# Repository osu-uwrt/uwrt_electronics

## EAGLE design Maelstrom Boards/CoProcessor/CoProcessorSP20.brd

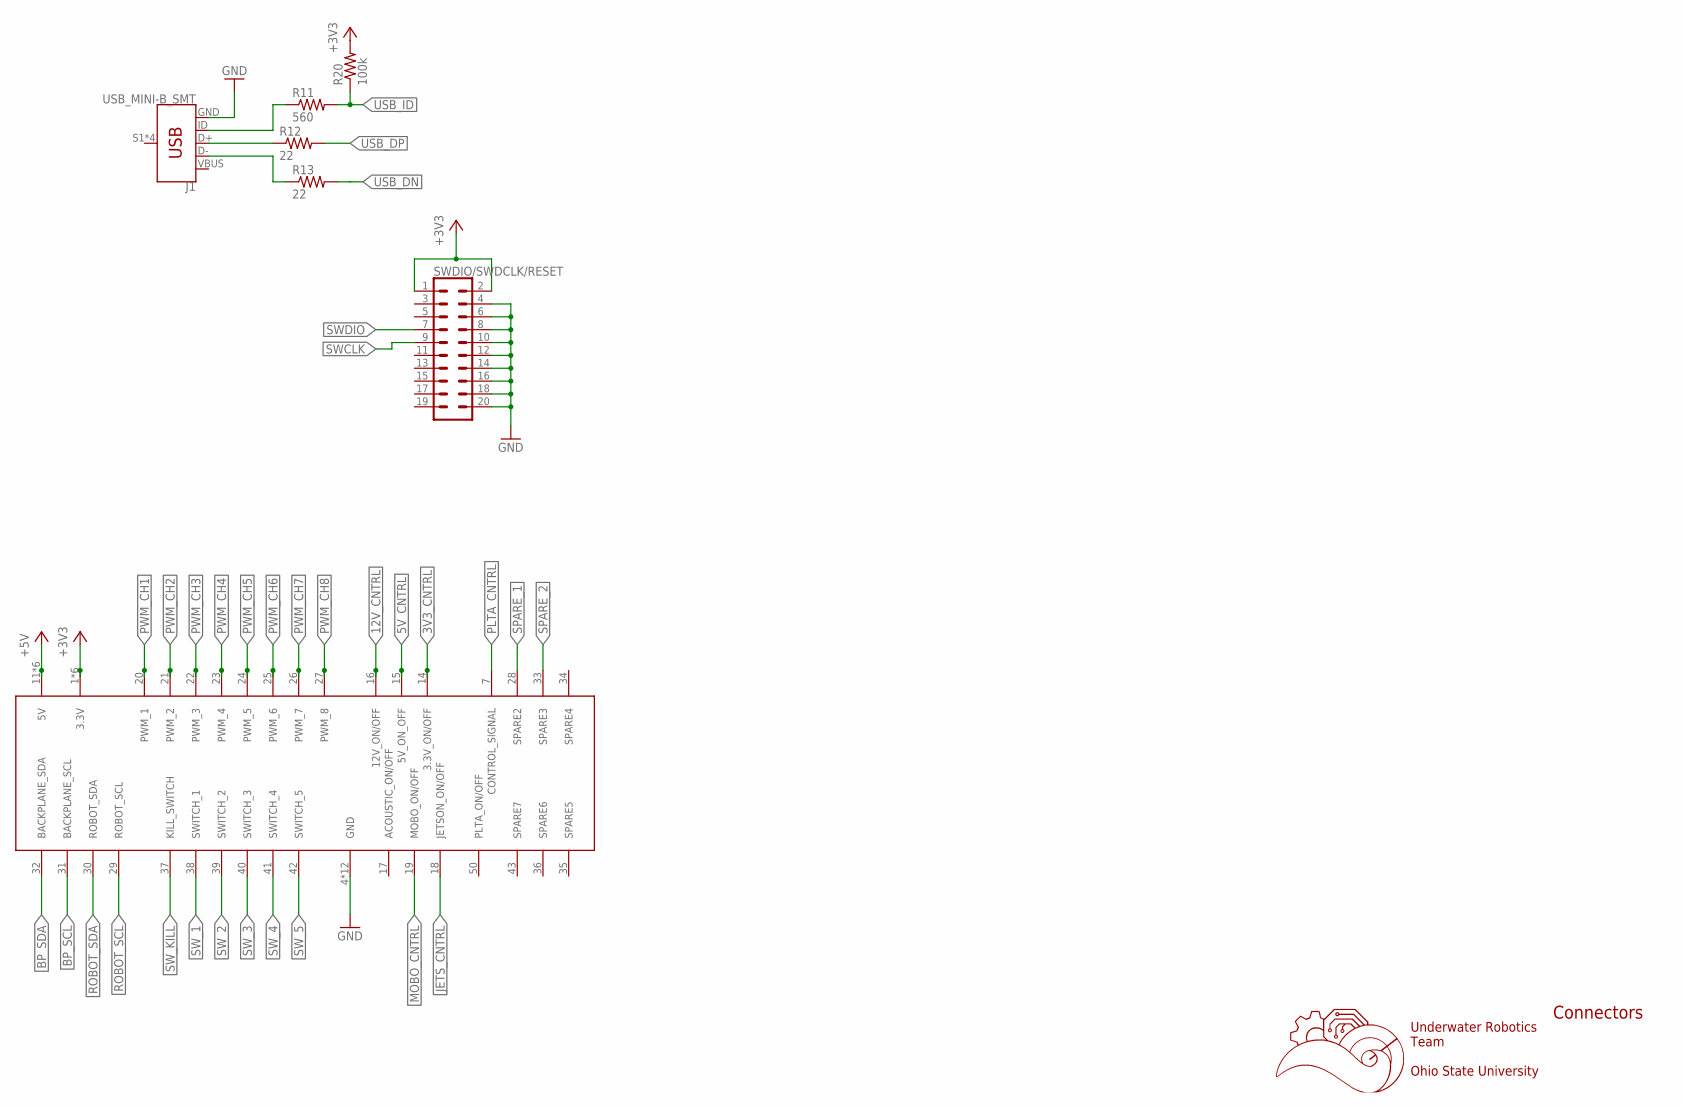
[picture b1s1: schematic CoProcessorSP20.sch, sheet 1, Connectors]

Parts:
J1: USB_MINI-B_SMT; USB-MINIB
R11: 560; R0603
R12, R13: 22; R0603
R20: 100k; R0603
SWDIO/SWDCLK/RESET: CONN_10X2; 2X10
U$1: 5530843-EDGE; 5530843-6-BOARDFINGERS

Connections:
3V3_CNTRL: U$1.14 (3.3V_ON/OFF); also elsewhere on the board
5V_CNTRL: U$1.15 (5V_ON_OFF); also elsewhere on the board
12V_CNTRL: U$1.16 (12V_ON/OFF); also elsewhere on the board
+3V3: R20.2, SWDIO/SWDCLK/RESET.1, SWDIO/SWDCLK/RESET.2, U$1.1 (3.3V), U$1.2 (3.3V), U$1.3 (3.3V), U$1.54 (3.3V), U$1.55 (3.3V), U$1.56 (3.3V); also elsewhere on the board
+5V: U$1.11 (5V), U$1.12 (5V), U$1.13 (5V), U$1.44 (5V), U$1.45 (5V), U$1.46 (5V)
BP_SCL: U$1.31 (BACKPLANE_SCL); also elsewhere on the board
BP_SDA: U$1.32 (BACKPLANE_SDA); also elsewhere on the board
GND: J1.GND, SWDIO/SWDCLK/RESET.4, SWDIO/SWDCLK/RESET.6, SWDIO/SWDCLK/RESET.8, SWDIO/SWDCLK/RESET.10, SWDIO/SWDCLK/RESET.12, SWDIO/SWDCLK/RESET.14, SWDIO/SWDCLK/RESET.16, SWDIO/SWDCLK/RESET.18, SWDIO/SWDCLK/RESET.20, U$1.4 (GND), U$1.5 (GND), U$1.6 (GND), U$1.8 (GND), U$1.9 (GND), U$1.10 (GND), U$1.47 (GND), U$1.48 (GND), U$1.49 (GND), U$1.51 (GND), U$1.52 (GND), U$1.53 (GND); also elsewhere on the board
JETS_CNTRL: U$1.18 (JETSON_ON/OFF); also elsewhere on the board
MOBO_CNTRL: U$1.19 (MOBO_ON/OFF); also elsewhere on the board
unnamed: J1.ID, R11.1
unnamed: J1.D+, R12.1
unnamed: J1.D-, R13.1
PLTA_CNTRL: U$1.7 (CONTROL_SIGNAL); also elsewhere on the board
PWM_CH1: U$1.20 (PWM_1); also elsewhere on the board
PWM_CH2: U$1.21 (PWM_2); also elsewhere on the board
PWM_CH3: U$1.22 (PWM_3); also elsewhere on the board
PWM_CH4: U$1.23 (PWM_4); also elsewhere on the board
PWM_CH5: U$1.24 (PWM_5); also elsewhere on the board
PWM_CH6: U$1.25 (PWM_6); also elsewhere on the board
PWM_CH7: U$1.26 (PWM_7); also elsewhere on the board
PWM_CH8: U$1.27 (PWM_8); also elsewhere on the board
ROBOT_SCL: U$1.29 (ROBOT_SCL); also elsewhere on the board
ROBOT_SDA: U$1.30 (ROBOT_SDA); also elsewhere on the board
SPARE_1: U$1.28 (SPARE2); also elsewhere on the board
SPARE_2: U$1.33 (SPARE3); also elsewhere on the board
SWCLK: SWDIO/SWDCLK/RESET.9; also elsewhere on the board
SWDIO: SWDIO/SWDCLK/RESET.7; also elsewhere on the board
SW_1: U$1.38 (SWITCH_1); also elsewhere on the board
SW_2: U$1.39 (SWITCH_2); also elsewhere on the board
SW_3: U$1.40 (SWITCH_3); also elsewhere on the board
SW_4: U$1.41 (SWITCH_4); also elsewhere on the board
SW_5: U$1.42 (SWITCH_5); also elsewhere on the board
SW_KILL: U$1.37 (KILL_SWITCH); also elsewhere on the board
USB_DN: R13.2; also elsewhere on the board
USB_DP: R12.2; also elsewhere on the board
USB_ID: R11.2, R20.1
VBUS: J1.VBUS

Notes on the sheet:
Underwater Robotics Team Ohio State University
Connectors

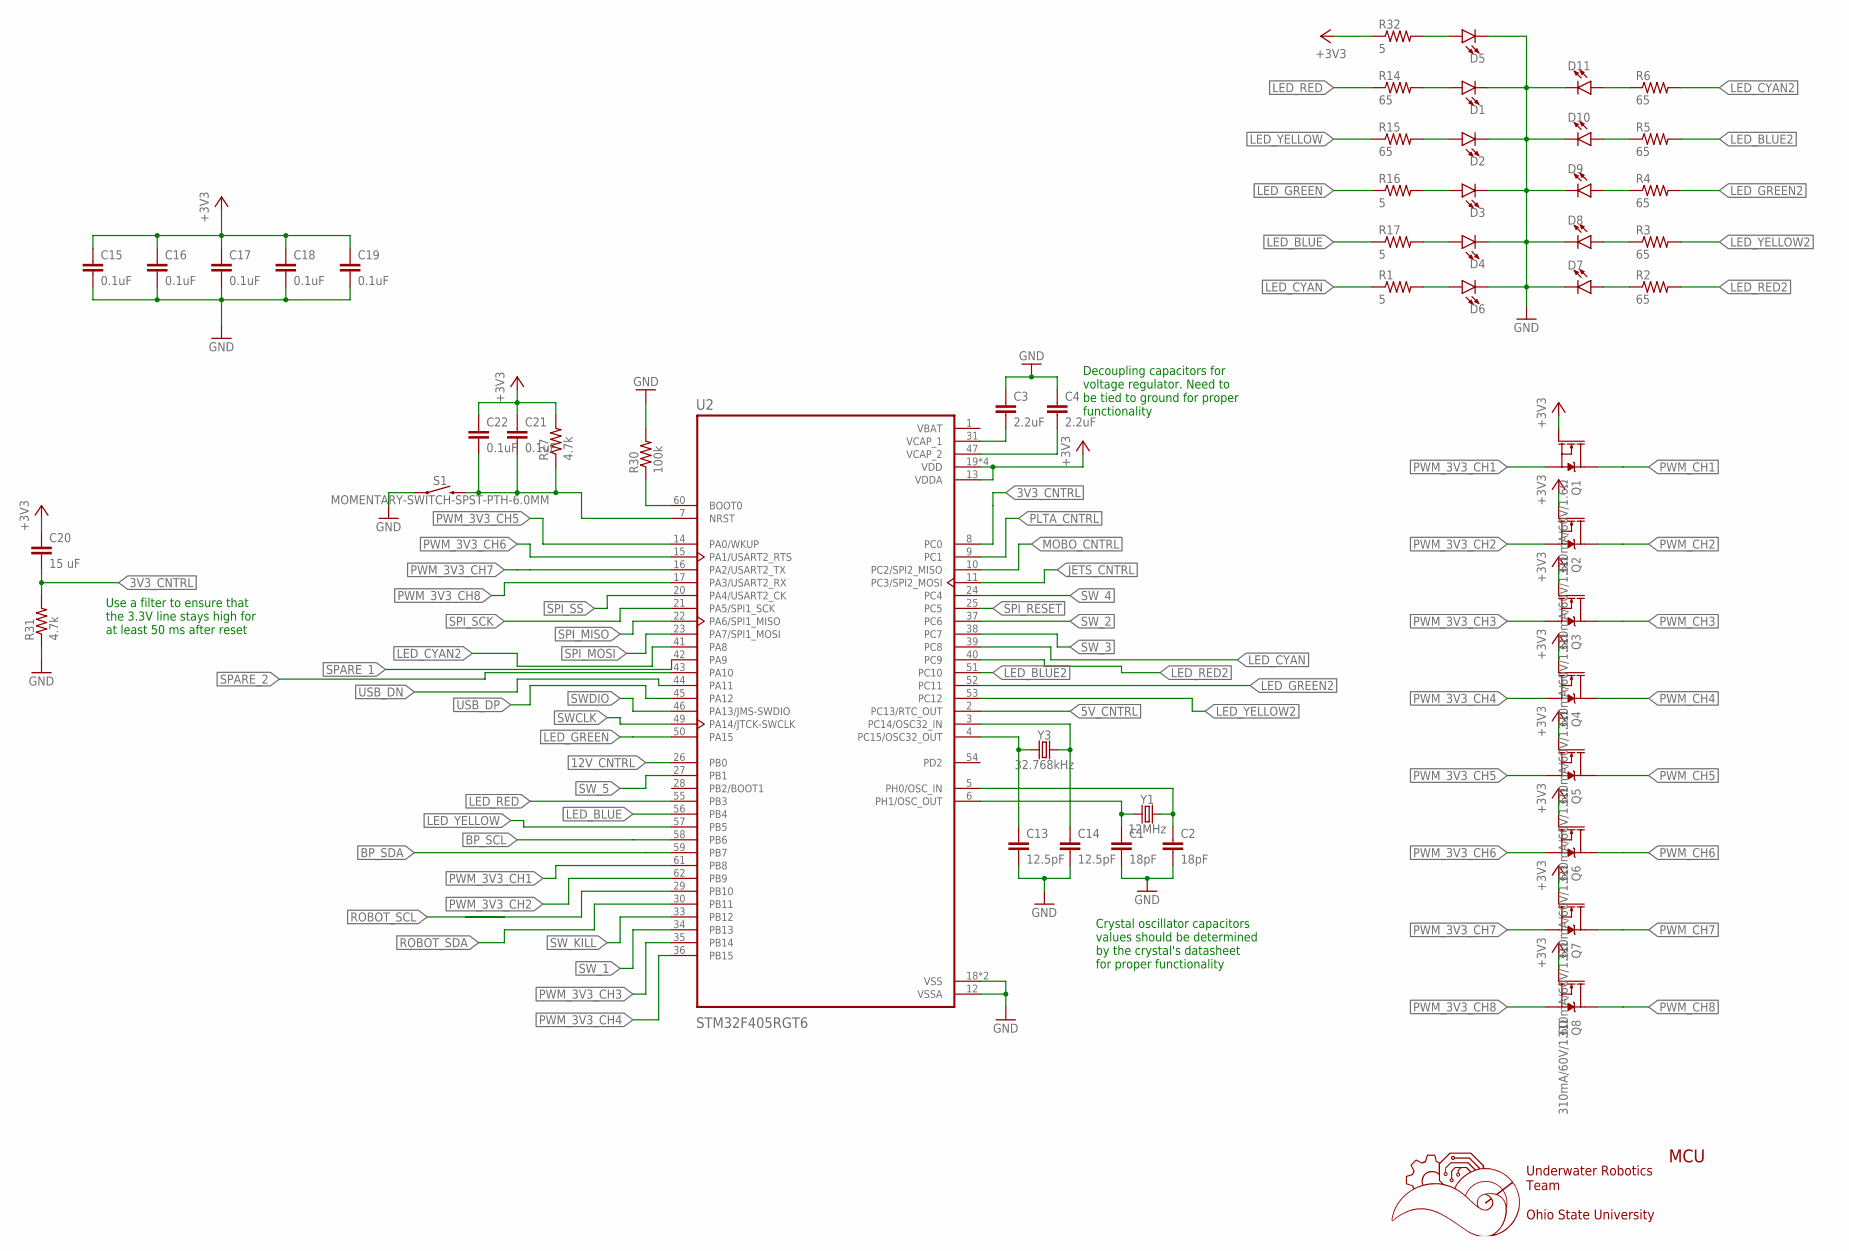
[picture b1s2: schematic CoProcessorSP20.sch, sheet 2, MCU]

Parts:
C1, C2: 18pF; C0603
C3, C4: 2.2uF; C0603
C13, C14: 12.5pF; C0603
C15, C16, C17, C18, C19, C21, C22: 0.1uF; C0603
C20: 15 uF; C050-025X075
D1, D2, D3, D4, D5, D6, D7, D8, D9, D10, D11: LED0603; LED-0603
Q1, Q2, Q3, Q4, Q5, Q6, Q7, Q8: 310mA/60V/1.6Ω; SOT323
R1, R16, R17, R32: 5; R0603
R2, R3, R4, R5, R6, R14, R15: 65; R0603
R27, R31: 4.7k; R0603
R30: 100k; R0603
S1: MOMENTARY-SWITCH-SPST-PTH-6.0MM; TACTILE_SWITCH_PTH_6.0MM
U2: STM32F405RGT6; QFP50P1200X1200X160-64N
Y1: 12MHz; HC49US
Y3: 32.768kHz; CRYSTAL-SMD-3.2X1.5MM

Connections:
3V3_CNTRL: C20.2, R31.2, U2.8 (PC0); also elsewhere on the board
5V_CNTRL: U2.2 (PC13/RTC_OUT); also elsewhere on the board
12V_CNTRL: U2.26 (PB0); also elsewhere on the board
+3V3: C15.1, C16.1, C17.1, C18.1, C19.1, C20.1, C21.1, C22.1, Q1.1 (G), Q2.1 (G), Q3.1 (G), Q4.1 (G), Q5.1 (G), Q6.1 (G), Q7.1 (G), Q8.1 (G), R27.2, R32.1, U2.13 (VDDA), U2.19 (VDD), U2.32 (VDD), U2.48 (VDD), U2.64 (VDD); also elsewhere on the board
BP_SCL: U2.58 (PB6); also elsewhere on the board
BP_SDA: U2.59 (PB7); also elsewhere on the board
GND: C1.2, C2.2, C3.1, C4.1, C13.2, C14.2, C15.2, C16.2, C17.2, C18.2, C19.2, D1.C, D2.C, D3.C, D4.C, D5.C, D6.C, D7.C, D8.C, D9.C, D10.C, D11.C, R30.2, R31.1, S1.1, U2.12 (VSSA), U2.18 (VSS), U2.63 (VSS); also elsewhere on the board
JETS_CNTRL: U2.11 (PC3/SPI2_MOSI); also elsewhere on the board
LED_BLUE: R17.1, U2.56 (PB4)
LED_BLUE2: R5.2, U2.51 (PC10)
LED_CYAN: R1.1, U2.39 (PC8)
LED_CYAN2: R6.2, U2.41 (PA8)
LED_GREEN: R16.1, U2.50 (PA15)
LED_GREEN2: R4.2, U2.52 (PC11)
LED_RED: R14.1, U2.55 (PB3)
LED_RED2: R2.2, U2.40 (PC9)
LED_YELLOW: R15.1, U2.57 (PB5)
LED_YELLOW2: R3.2, U2.53 (PC12)
MOBO_CNTRL: U2.10 (PC2/SPI2_MISO); also elsewhere on the board
unnamed: C1.1, U2.6 (PH1/OSC_OUT), Y1.1
unnamed: D1.A, R14.2
unnamed: D2.A, R15.2
unnamed: D3.A, R16.2
unnamed: D4.A, R17.2
unnamed: C2.1, U2.5 (PH0/OSC_IN), Y1.2
unnamed: C4.2, U2.47 (VCAP_2)
unnamed: C3.2, U2.31 (VCAP_1)
unnamed: C13.1, U2.4 (PC15/OSC32_OUT), Y3.P$1 (1)
unnamed: C14.1, U2.3 (PC14/OSC32_IN), Y3.P$2 (2)
unnamed: R30.1, U2.60 (BOOT0)
unnamed: D5.A, R32.2
unnamed: D6.A, R1.2
unnamed: D7.A, R2.1
unnamed: C21.2, C22.2, R27.1, S1.3 (2), U2.7 (NRST)
unnamed: D8.A, R3.1
unnamed: D9.A, R4.1
unnamed: D10.A, R5.1
unnamed: D11.A, R6.1
PLTA_CNTRL: U2.9 (PC1); also elsewhere on the board
PWM_3V3_CH1: Q1.2 (S), U2.61 (PB8)
PWM_3V3_CH2: Q2.2 (S), U2.62 (PB9)
PWM_3V3_CH3: Q3.2 (S), U2.35 (PB14)
PWM_3V3_CH4: Q4.2 (S), U2.36 (PB15)
PWM_3V3_CH5: Q5.2 (S), U2.14 (PA0/WKUP)
PWM_3V3_CH6: Q6.2 (S), U2.15 (PA1/USART2_RTS)
PWM_3V3_CH7: Q7.2 (S), U2.16 (PA2/USART2_TX)
PWM_3V3_CH8: Q8.2 (S), U2.17 (PA3/USART2_RX)
PWM_CH1: Q1.3 (D); also elsewhere on the board
PWM_CH2: Q2.3 (D); also elsewhere on the board
PWM_CH3: Q3.3 (D); also elsewhere on the board
PWM_CH4: Q4.3 (D); also elsewhere on the board
PWM_CH5: Q5.3 (D); also elsewhere on the board
PWM_CH6: Q6.3 (D); also elsewhere on the board
PWM_CH7: Q7.3 (D); also elsewhere on the board
PWM_CH8: Q8.3 (D); also elsewhere on the board
ROBOT_SCL: U2.29 (PB10); also elsewhere on the board
ROBOT_SDA: U2.30 (PB11); also elsewhere on the board
SPARE_1: U2.42 (PA9); also elsewhere on the board
SPARE_2: U2.43 (PA10); also elsewhere on the board
SPI_MISO: U2.22 (PA6/SPI1_MISO); also elsewhere on the board
SPI_MOSI: U2.23 (PA7/SPI1_MOSI); also elsewhere on the board
SPI_RESET: U2.25 (PC5); also elsewhere on the board
SPI_SCK: U2.21 (PA5/SPI1_SCK); also elsewhere on the board
SPI_SS: U2.20 (PA4/USART2_CK); also elsewhere on the board
SWCLK: U2.49 (PA14/JTCK-SWCLK); also elsewhere on the board
SWDIO: U2.46 (PA13/JMS-SWDIO); also elsewhere on the board
SW_1: U2.34 (PB13); also elsewhere on the board
SW_2: U2.37 (PC6); also elsewhere on the board
SW_3: U2.38 (PC7); also elsewhere on the board
SW_4: U2.24 (PC4); also elsewhere on the board
SW_5: U2.27 (PB1); also elsewhere on the board
SW_KILL: U2.33 (PB12); also elsewhere on the board
USB_DN: U2.44 (PA11); also elsewhere on the board
USB_DP: U2.45 (PA12); also elsewhere on the board
VBAT: U2.1 (VBAT)

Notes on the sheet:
Underwater Robotics Team Ohio State University
MCU
Decoupling capacitors for voltage regulator. Need to be tied to ground for proper functionality
Crystal oscillator capacitors values should be determined by the crystal's datasheet for proper functionality
Use a filter to ensure that the 3.3V line stays high for at least 50 ms after reset

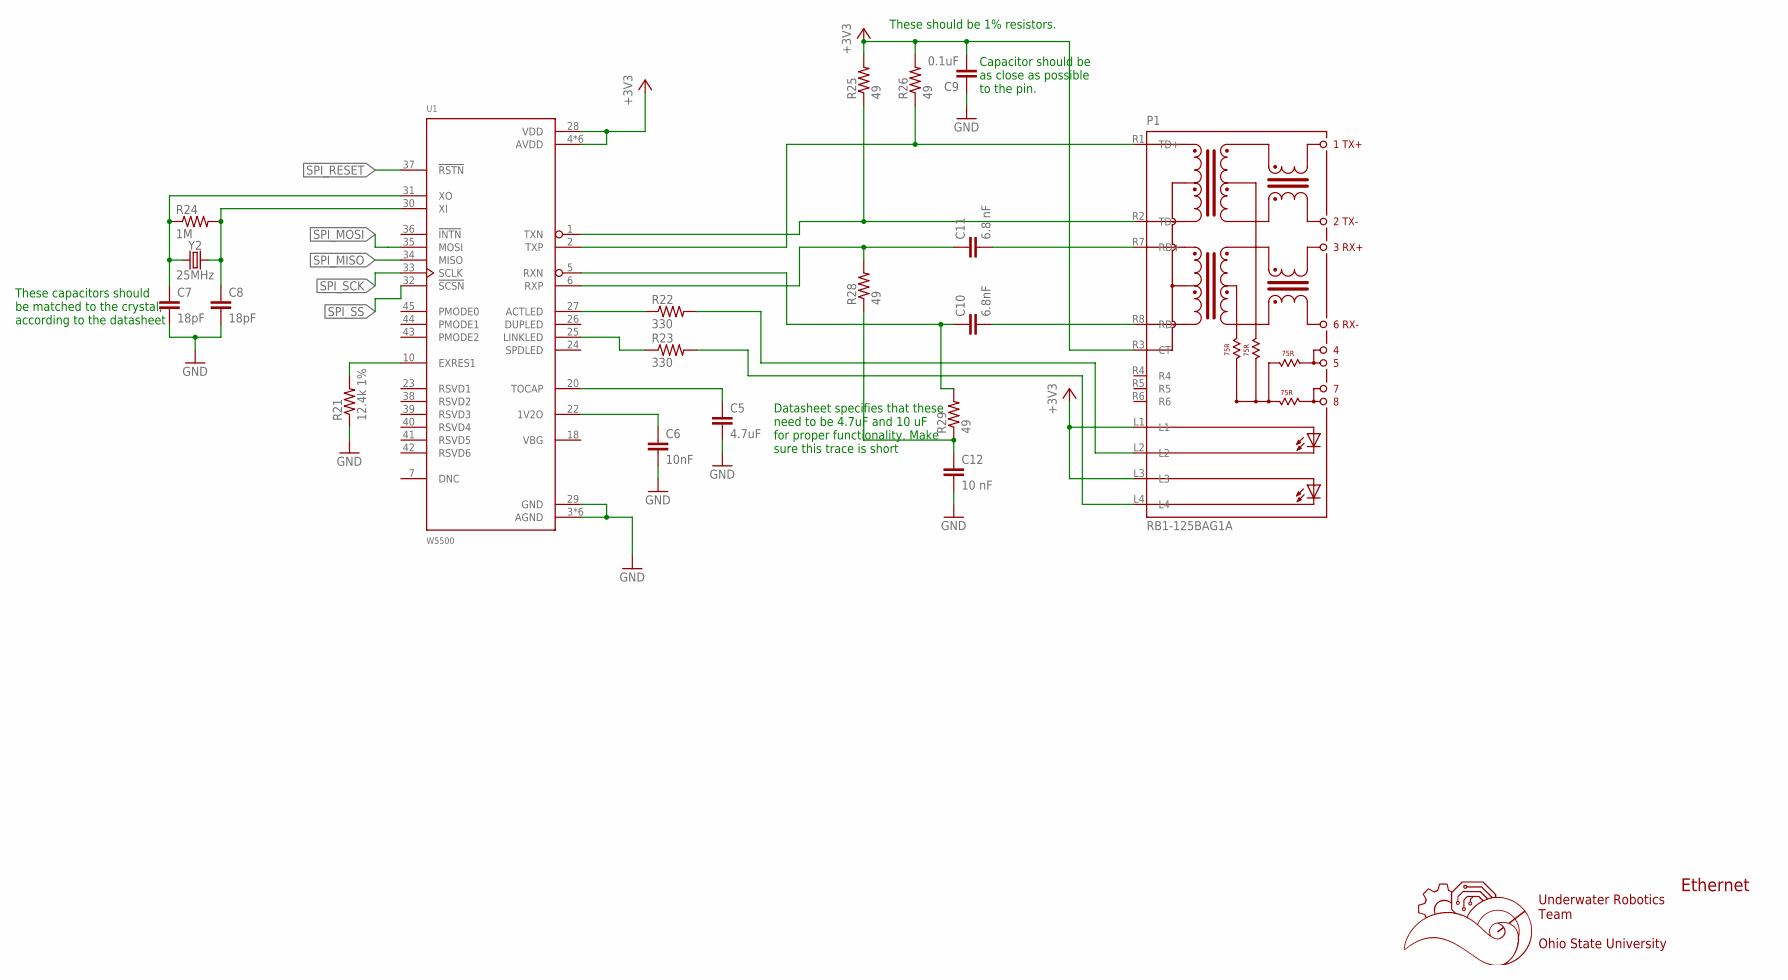
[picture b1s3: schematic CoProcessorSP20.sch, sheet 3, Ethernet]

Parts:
C5: 4.7uF; C0603
C6: 10nF; C0603
C7, C8: 18pF; C0603
C9: 0.1uF; C0603
C10: 6.8nF; C0603
C11: 6.8 nF; C0603
C12: 10 nF; C0603
P1: RB1-125BAG1A; WIZNET_RB1-125BAG1A
R21: 12.4k 1%; R0603
R22, R23: 330; R0603
R24: 1M; R0603
R25, R26, R28, R29: 49; R0603
U1: W5500; QFP50P900X900X160-48N
Y2: 25MHz; HC49US

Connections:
+3V3: C9.2, P1.L1, P1.L3, P1.R3 (CT), R25.2, R26.2, U1.4 (AVDD), U1.8 (AVDD), U1.11 (AVDD), U1.15 (AVDD), U1.17 (AVDD), U1.21 (AVDD), U1.28 (VDD); also elsewhere on the board
GND: C5.2, C6.2, C7.2, C8.2, C9.1, C12.2, R21.1, U1.3 (AGND), U1.9 (AGND), U1.14 (AGND), U1.16 (AGND), U1.19 (AGND), U1.29 (GND), U1.48 (AGND); also elsewhere on the board
unnamed: C5.1, U1.20 (TOCAP)
unnamed: C6.1, U1.22 (1V2O)
unnamed: R21.2, U1.10 (EXRES1)
unnamed: P1.R2 (TD-), R25.1, U1.1 (TXN)
unnamed: P1.R1 (TD+), R26.1, U1.2 (TXP)
unnamed: C10.1, R29.2, U1.5 (RXN)
unnamed: C11.1, R28.2, U1.6 (RXP)
unnamed: P1.L2, R22.2
unnamed: P1.L4, R23.2
unnamed: R22.1, U1.27 (ACTLED)
unnamed: R23.1, U1.25 (LINKLED)
unnamed: C8.1, R24.2, U1.30 (XI), Y2.2
unnamed: C7.1, R24.1, U1.31 (XO), Y2.1
unnamed: C10.2, P1.R8 (RD-)
unnamed: C11.2, P1.R7 (RD+)
unnamed: C12.1, R28.1, R29.1
SPI_MISO: U1.34 (MISO); also elsewhere on the board
SPI_MOSI: U1.35 (MOSI); also elsewhere on the board
SPI_RESET: U1.37 (!RSTN); also elsewhere on the board
SPI_SCK: U1.33 (SCLK); also elsewhere on the board
SPI_SS: U1.32 (!SCSN); also elsewhere on the board

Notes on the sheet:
Underwater Robotics Team Ohio State University
Ethernet
Datasheet specifies that these need to be 4.7uF and 10 uF for proper functionality. Make sure this trace is short
These capacitors should be matched to the crystal, according to the datasheet
These should be 1% resistors.
Capacitor should be as close as possible to the pin.

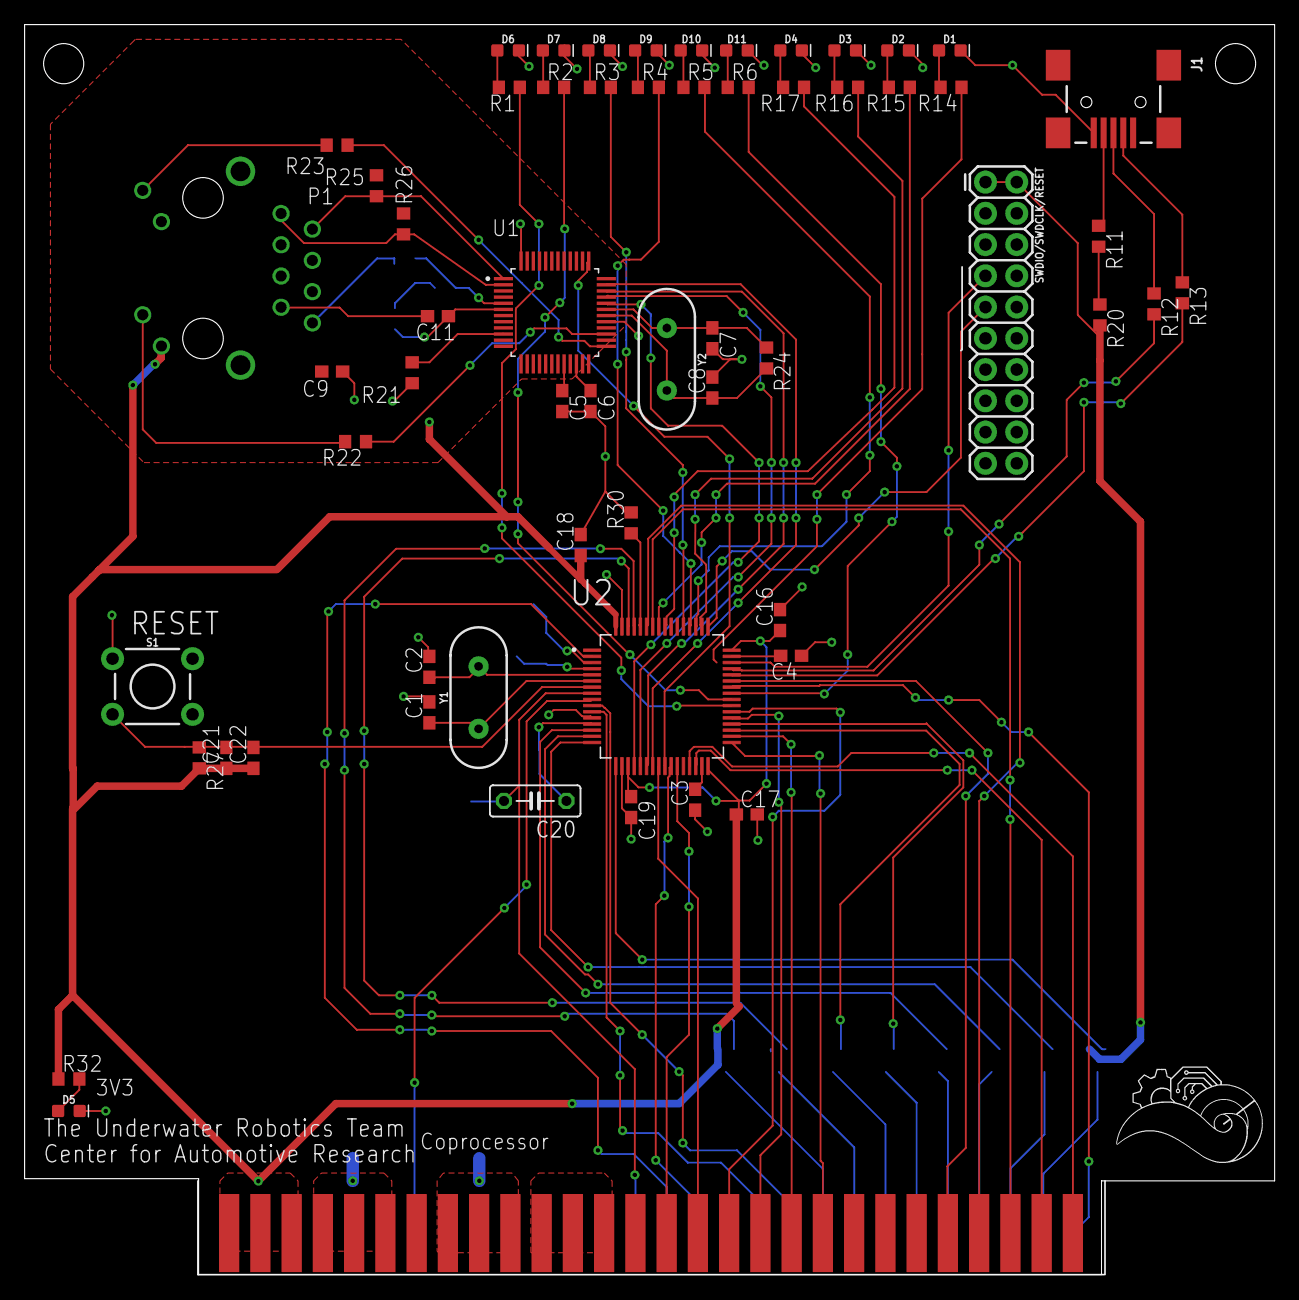
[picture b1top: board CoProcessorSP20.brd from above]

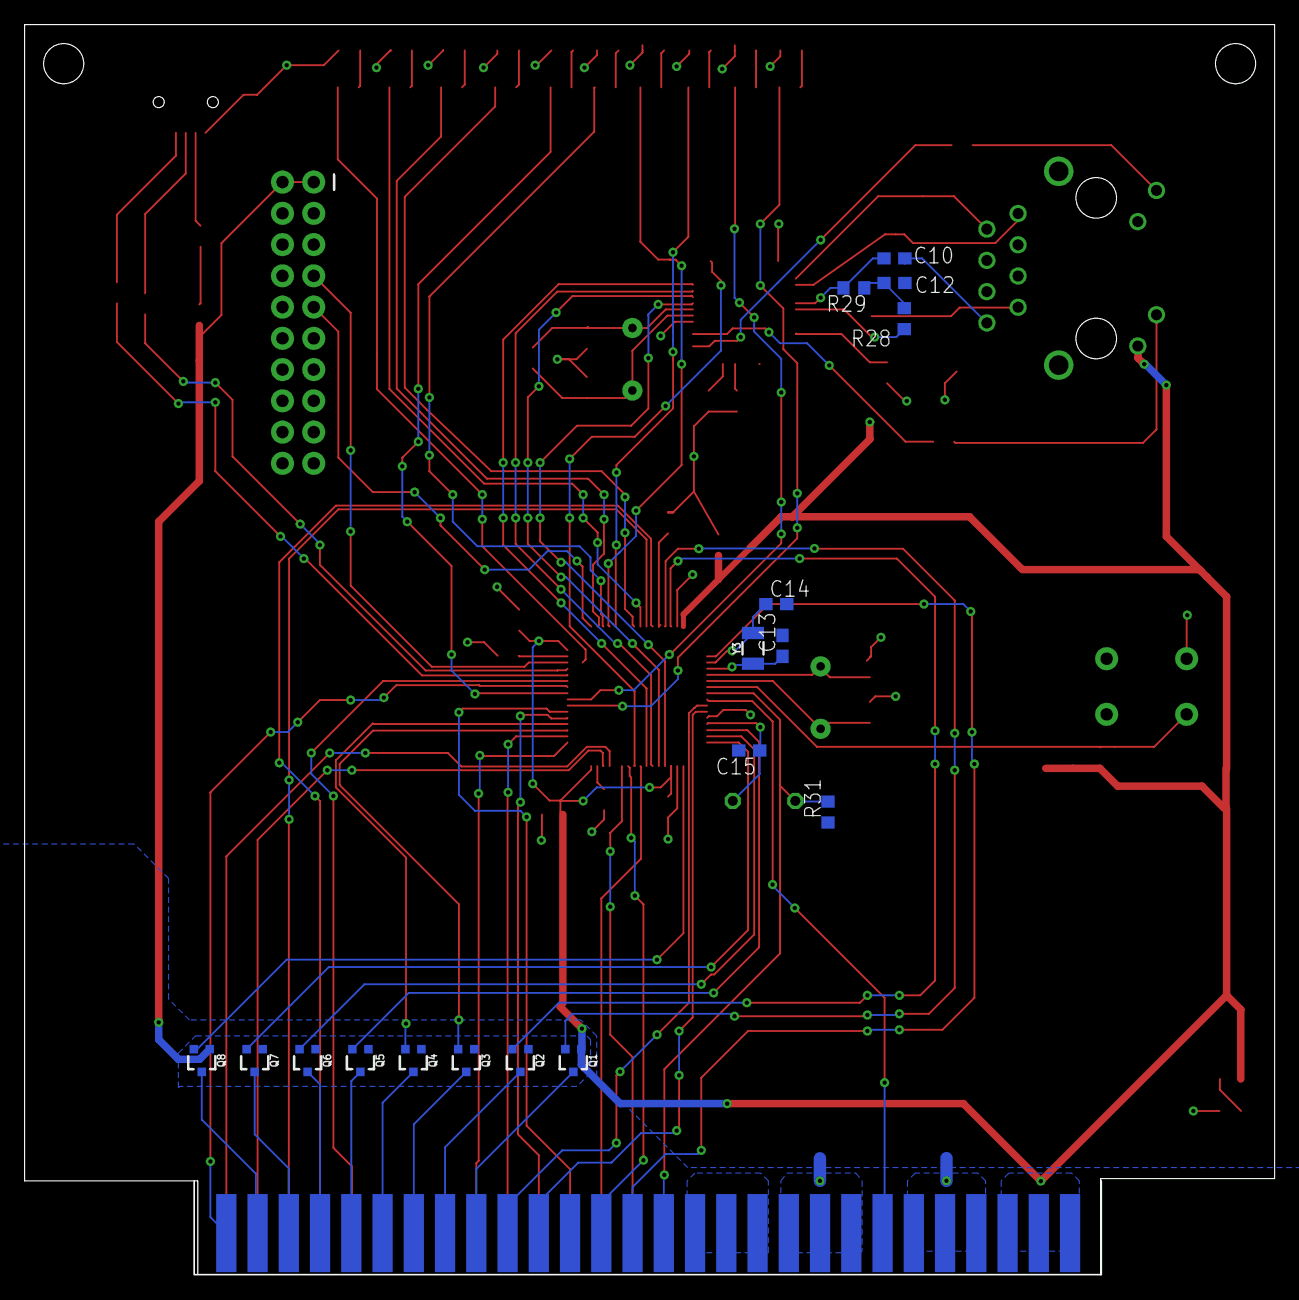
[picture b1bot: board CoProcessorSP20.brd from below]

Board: 2 copper layers, 101.6 x 101.6 mm, 77 parts (17 on the bottom side), 95 nets.

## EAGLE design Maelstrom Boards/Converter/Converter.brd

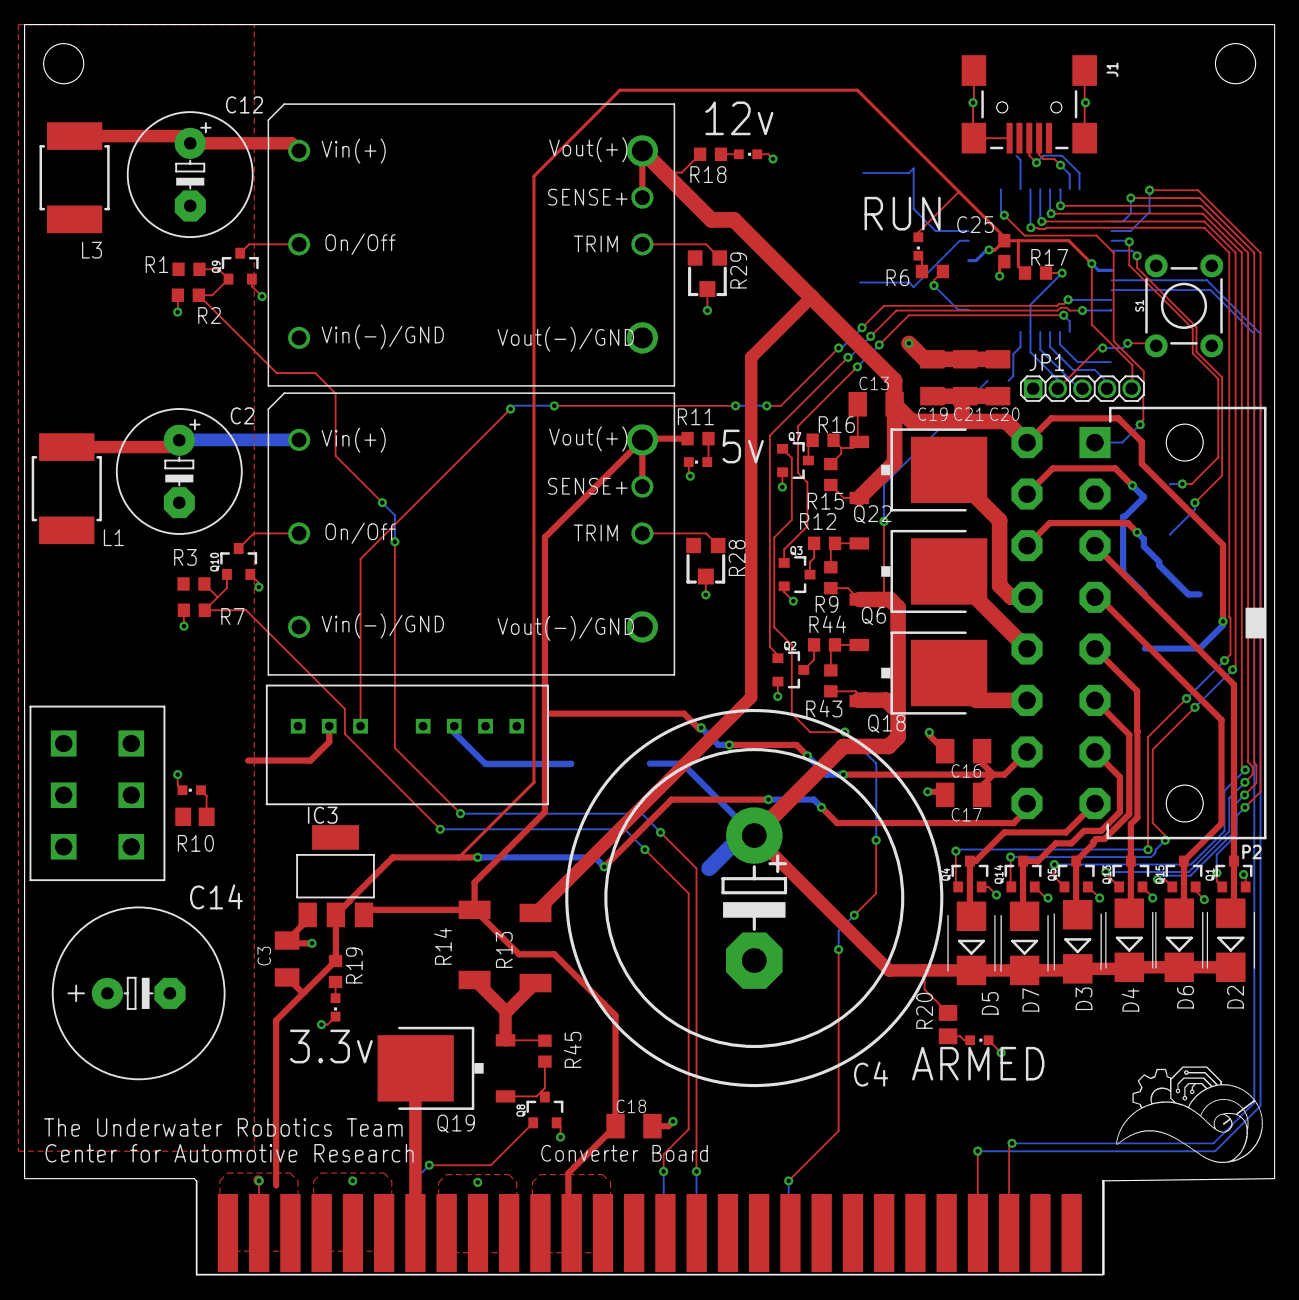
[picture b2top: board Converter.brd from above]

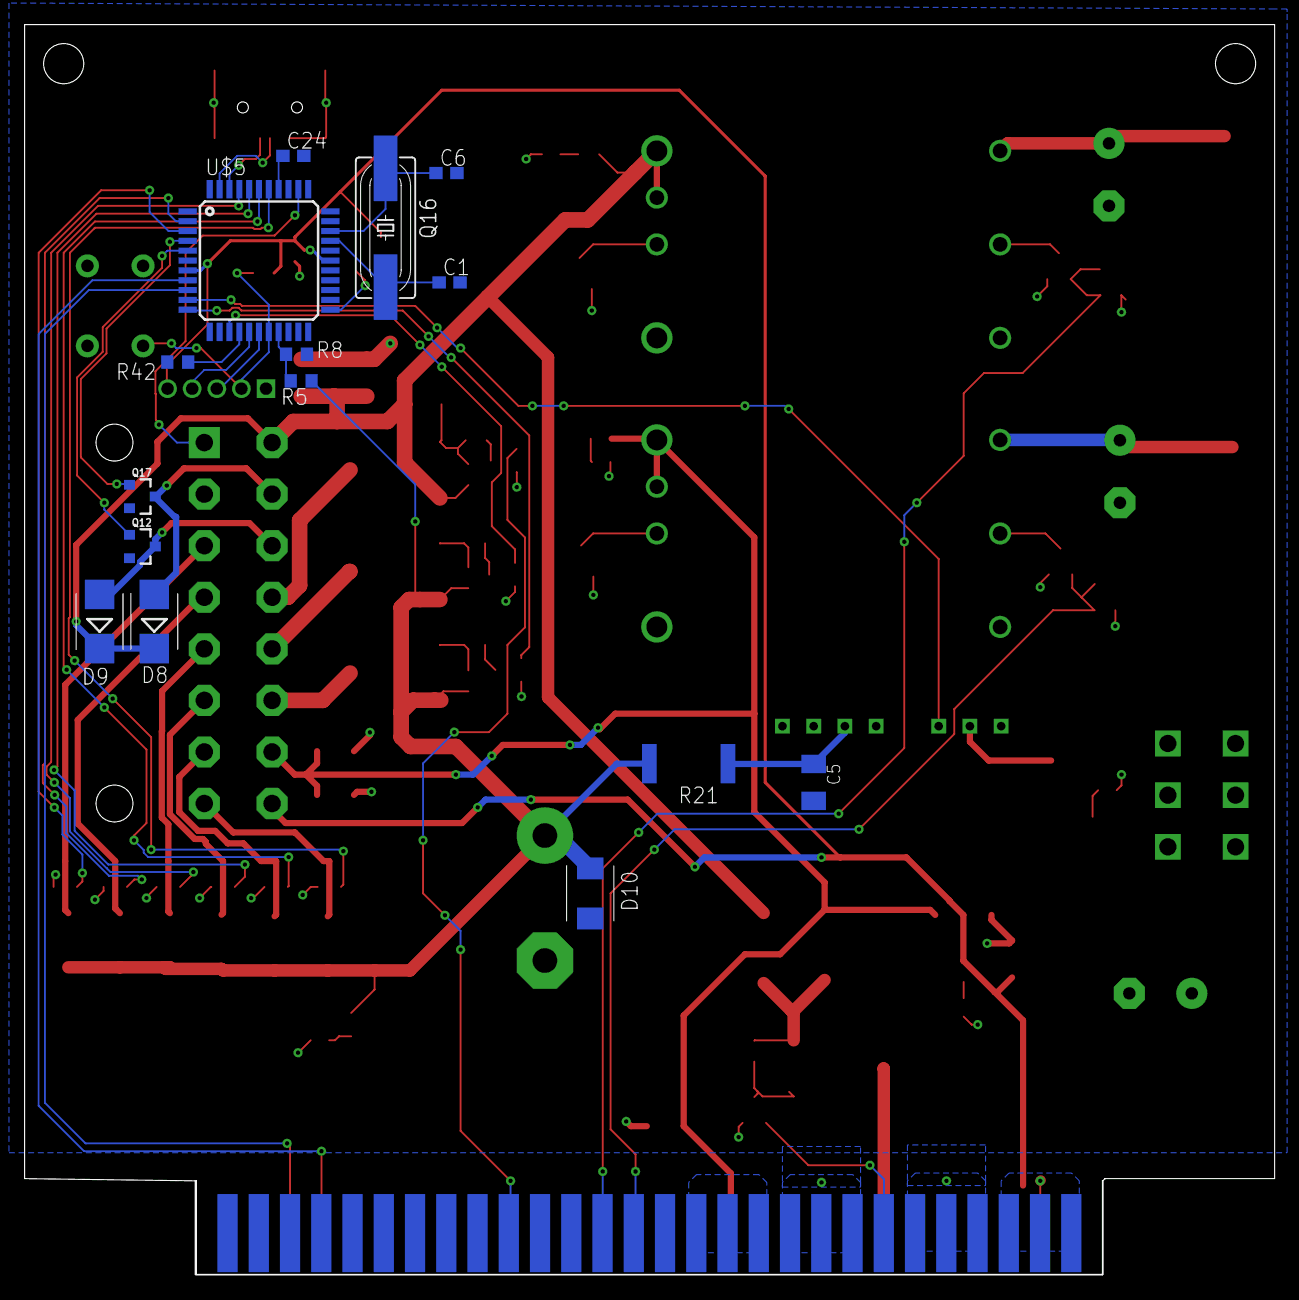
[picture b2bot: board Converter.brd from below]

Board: 2 copper layers, 101.6 x 101.6 mm, 90 parts (15 on the bottom side), 68 nets.

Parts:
3V3, 5V_LED, 12V_LED: CHIPLED_0603
5VCONVERTER, 12VCONVERTER: CONVERTER
ARMED: CHIPLED_0603
BATTERY: CHIPLED_0603
C1, C6: 30pF; C0603
C2, C12: 330 uF; E5-10,5
C3, C5, C13, C16, C17, C18, C19, C20, C21: 47 uF; C1206K
C4: 22mF; EB30D
C14: 1000 uF; E5-13
C24: 220nF; C0603
C25: 100nF; C0603
D2, D3, D4, D5, D6, D7, D8, D9: SMB
D10: SMBJ
IC3: REG1117; SOT223
J1: USB-MINIB
JP1: 1_05X2MM
L1, L3: 1 uH; MS85
P2: 39-30-16?; 39-30-?16?
Q1, Q2, Q3, Q4, Q5, Q7, Q8, Q9, Q10, Q12, Q13, Q14, Q15, Q17: SOT23-3
Q6, Q18, Q19, Q22: TO252
Q16: HC49UP
R1, R3, R5: 100K; R0603
R2, R7: 13K; R0603
R6, R19: 5; R0603
R8, R42: 10K; R0603
R9, R12, R15, R16, R17, R43, R44, R45: 10k; R0603
R10, R20: 1.2k; R0805
R11: 90; R0603
R13, R14: 0; M2309
R18: 470; R0603
R21: 120; R6332W
R28, R29: RTRIM3103
RUN: CHIPLED_0603
S1: TACTILE_SWITCH_PTH_6.0MM
U$1: 5530843-EDGE; 5530843-6-BOARDFINGERS
U$3: 6PIN-VERT; 6PIN_VERT
U$5: 18F4550; TQFP-44A-44
U$6: TMR6-2415

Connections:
5VON: Q10.1, R3.2, R7.2, U$1.15
12VON: Q9.1, R1.2, R2.2, U$1.16
!MCLR!: JP1.2, R17.2, S1.1, U$5.18
+3V3: C3.1, C25.1, IC3.2, JP1.5, P2.16, R17.1, R19.2, RUN.A, U$1.1, U$1.2, U$1.3, U$1.54, U$1.55, U$1.56, U$5.7, U$5.28
+5V: 5VCONVERTER.7,SENSE+, 5VCONVERTER.8,VOUT(+), C16.1, C17.1, C18.1, IC3.3, P2.15, R11.2, R14.2, U$1.11, U$1.12, U$1.13, U$1.44, U$1.45, U$1.46
+12V: 12VCONVERTER.7,SENSE+, 12VCONVERTER.8,VOUT(+), C13.1, C19.1, C20.1, C21.1, D8.C, D9.C, P2.9, Q22.2, R13.2, R15.2, R18.2
+24V: C4.+, D2.C, D3.C, D4.C, D5.C, D6.C, D7.C, D10.C, Q6.2, Q18.2, R5.1, R9.2, R20.2, R21.2, R43.2
AGND: 3V3.C, 5VCONVERTER.3,VIN(-)/GND, 5VCONVERTER.4,VOUT(-)/GND, 5V_LED.C, 12VCONVERTER.3,VIN(-)/GND, 12VCONVERTER.4,VOUT(-)/GND, 12V_LED.C, ARMED.C, BATTERY.C, C1.2, C2.-, C3.2, C4.-, C5.2, C6.2, C12.-, C14.-, C16.2, C17.2, C18.2, C19.2, C20.2, C21.2, C24.2, C25.2, D10.A, IC3.1, J1.GND, J1.S1, J1.S2, J1.S3, J1.S4, JP1.1, P2.2, Q1.2, Q2.2, Q3.2, Q4.2, Q5.2, Q7.2, Q8.2, Q9.2, Q10.2, Q12.2, Q13.2, Q14.2, Q15.2, Q17.2, R2.1, R7.1, R8.2, R28.2, R29.2, R42.2, S1.3, U$1.4, U$1.5, U$1.6, U$1.8, U$1.9, U$1.10, U$1.47, U$1.48, U$1.49, U$1.51, U$1.52, U$1.53, U$3.1-, U$3.2-, U$3.3-, U$5.6, U$5.29, U$6.P$1, U$6.P$7
ARM_TORPEDO: U$5.10, U$6.P$3
COIL_1: D5.A, P2.8, Q4.3
COIL_1_GATE: Q4.1, U$5.38
COIL_2: D7.A, P2.7, Q14.3
COIL_2_GATE: Q14.1, U$5.39
COIL_3: D3.A, P2.6, Q5.3
COIL_3_GATE: Q5.1, U$5.40
COIL_4: D4.A, P2.5, Q13.3
COIL_4_GATE: Q13.1, U$5.41
COIL_5: D6.A, P2.4, Q15.3
COIL_5_GATE: Q15.1, U$5.2
COIL_S: D2.A, P2.3, Q1.3
COIL_S_GATE: Q1.1, U$5.3
DROPPER1: D8.A, P2.10, Q17.3
DROPPER1_GATE: Q17.1, U$5.4
DROPPER2: D9.A, P2.11, Q12.3
DROPPER2_GATE: Q12.1, U$5.5
MOBO_ON/OFF: Q7.1, U$1.19
MOBO_SWITCHED: P2.12, Q22.3
unnamed: 12VCONVERTER.6,TRIM, R29.1
unnamed: 5VCONVERTER.6,TRIM, R28.1
unnamed: 12VCONVERTER.1,VIN(+), C12.+, L3.2
unnamed: R5.2, R8.1, U$5.19
unnamed: 3V3.A, R19.1
unnamed: 5V_LED.A, R11.1
unnamed: 5VCONVERTER.1,VIN(+), C2.+, L1.2
unnamed: 12V_LED.A, R18.1
unnamed: BATTERY.A, R10.1
unnamed: ARMED.A, R20.1
unnamed: C13.2, Q22.1, R15.1, R16.2
unnamed: Q7.3, R16.1
unnamed: Q19.2, R13.1, R14.1, R45.2
unnamed: Q2.3, R44.1
unnamed: R6.2, RUN.C
unnamed: Q8.3, Q19.1, R45.1
unnamed: 12VCONVERTER.2,ON/OFF, Q9.3
unnamed: 5VCONVERTER.2,ON/OFF, Q10.3
unnamed: Q18.1, R43.1, R44.2
unnamed: C6.1, Q16.2, U$5.31
unnamed: C1.1, Q16.1, U$5.30
unnamed: R6.1, U$5.23
unnamed: Q6.1, R9.1, R12.2
unnamed: C5.1, R21.1, U$6.P$6
unnamed: Q3.3, R12.1
unnamed: C24.1, U$5.37
unnamed: R42.1, U$5.15
PGC: JP1.4, U$5.16
PGD: JP1.3, U$5.17
PLTA_ON/OFF: Q8.1, U$1.7
PLTA_SWITCHED: Q19.3, U$1.50
PWM: P2.1, U$5.35
SCL: U$1.31, U$5.9
SDA: U$1.32, U$5.8
TORPEDO1: P2.14, Q18.3
TORPEDO1_GATE: Q2.1, U$5.11
TORPEDO2: P2.13, Q6.3
TORPEDO2_GATE: Q3.1, U$5.14
USB+: J1.D+, U$5.43
USB-: J1.D-, U$5.42
V+: C14.+, L1.1, L3.1, R1.1, R3.1, R10.2, U$3.1+, U$3.2+, U$3.3+, U$6.P$2

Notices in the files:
parts and their libraries:
con-molex-mini-fit: Copyright (C) 2011, Bob Starr
SparkFun-DiscreteSemi: Licensing: Creative Commons ShareAlike 4.0 International - https://creativecommons.org/licenses/by-sa/4.0
